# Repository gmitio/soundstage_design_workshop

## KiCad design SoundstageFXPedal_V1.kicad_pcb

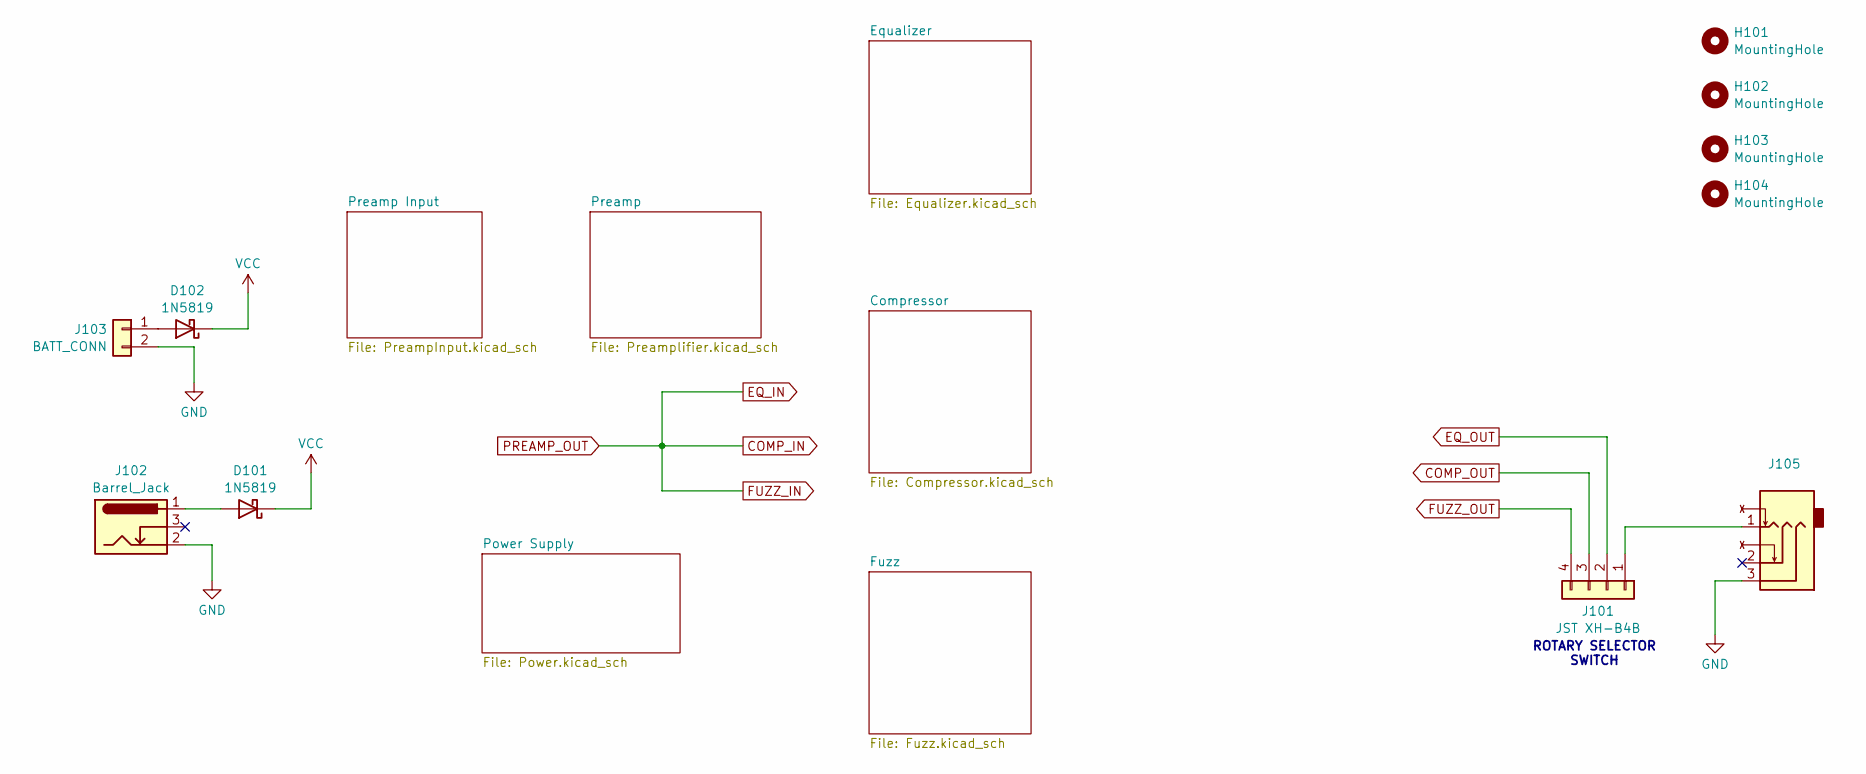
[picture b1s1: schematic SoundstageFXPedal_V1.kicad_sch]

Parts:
D101, D102: 1N5819; D_DO-41_SOD81_P10.16mm_Horizontal
H101, H102, H103, H104: MountingHole; MountingHole_4.3mm_M4_DIN965
J101: JST XH-B4B; JST_XH_B4B-XH-A_1x04_P2.50mm_Vertical
J102: Barrel_Jack; BarrelJack_Wuerth_6941xx301002
J103: BATT_CONN; PinHeader_1x02_P2.54mm_Vertical
J105: JST_XH_B3B-XH-A_1x03_P2.50mm_Vertical

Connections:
COMP_OUT: J101.3; also elsewhere on the board
EQ_OUT: J101.2; also elsewhere on the board
FUZZ_OUT: J101.4; also elsewhere on the board
GND: J102.2, J103.2, J105.3; also elsewhere on the board
unnamed: D101.2 (A), J102.1
unnamed: D102.2 (A), J103.1
unnamed: J101.1, J105.1
VCC: D101.1 (K), D102.1 (K); also elsewhere on the board

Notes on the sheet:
ROTARY SELECTOR SWITCH

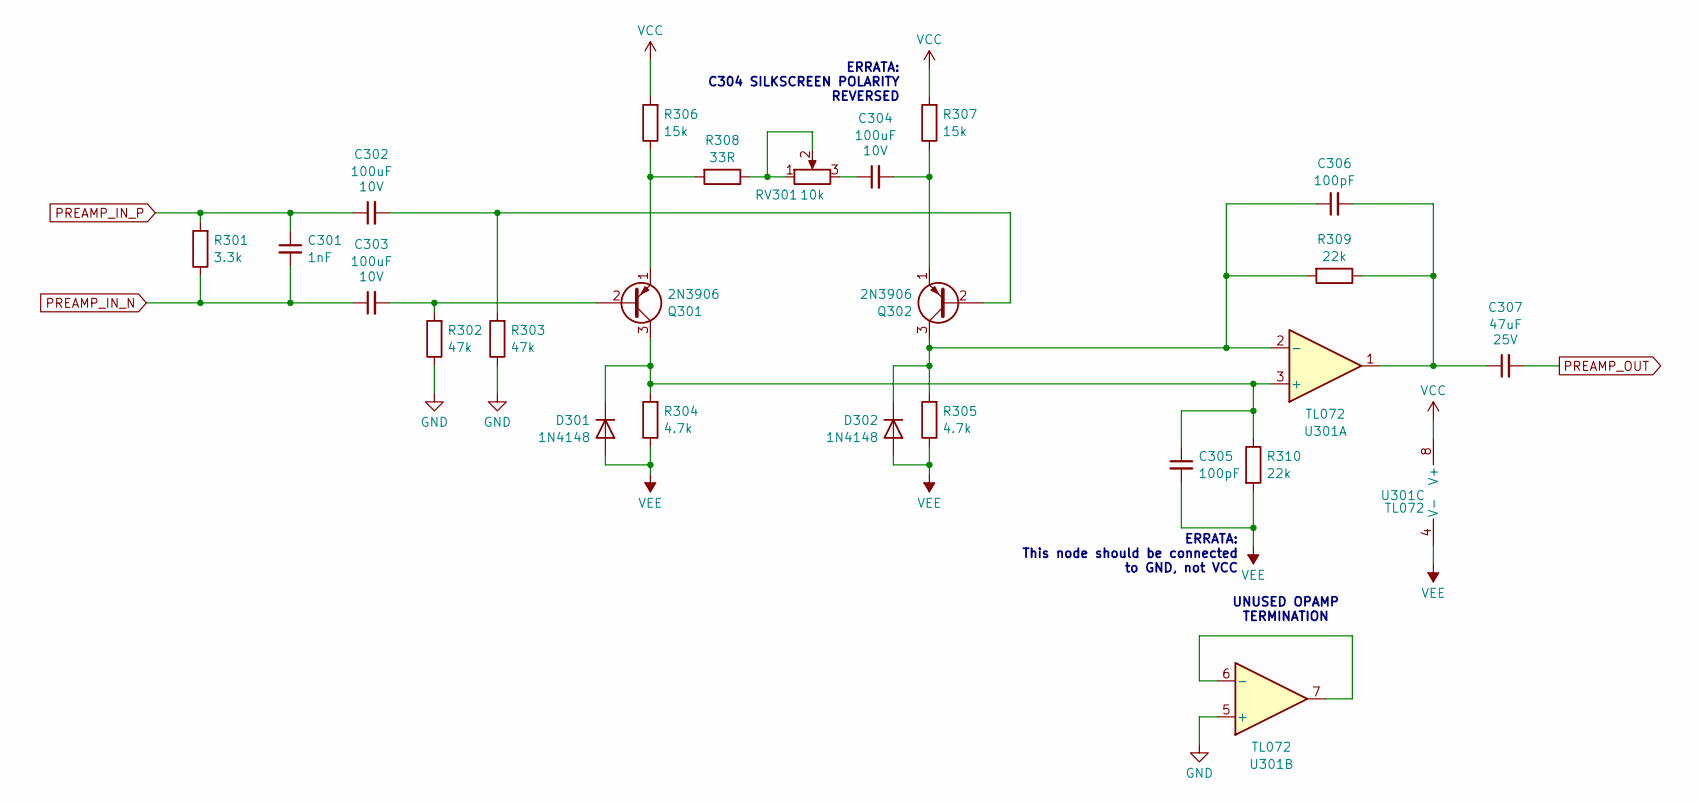
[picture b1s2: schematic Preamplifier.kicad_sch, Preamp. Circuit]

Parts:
C301: 1nF; C_Disc_D6.0mm_W4.4mm_P5.00mm
C302, C303, C304: 100uF; CP_Radial_D5.0mm_P2.00mm; Voltage 10V
C305, C306: 100pF; C_Disc_D5.0mm_W2.5mm_P2.50mm
C307: 47uF; CP_Radial_D5.0mm_P2.00mm; Voltage 25V; PartNo. MOUSER: 232-25PK47MEFC5X11
D301, D302: 1N4148; D_DO-35_SOD27_P7.62mm_Horizontal
Q301, Q302: 2N3906; TO-92_Inline_Wide
R301: 3.3k; R_Axial_DIN0207_L6.3mm_D2.5mm_P7.62mm_Horizontal
R302, R303: 47k; R_Axial_DIN0207_L6.3mm_D2.5mm_P7.62mm_Horizontal
R304, R305: 4.7k; R_Axial_DIN0207_L6.3mm_D2.5mm_P7.62mm_Horizontal
R306, R307: 15k; R_Axial_DIN0207_L6.3mm_D2.5mm_P7.62mm_Horizontal
R308: 33R; R_Axial_DIN0207_L6.3mm_D2.5mm_P7.62mm_Horizontal
R309, R310: 22k; R_Axial_DIN0207_L6.3mm_D2.5mm_P7.62mm_Horizontal
RV301: 10k; JST_XH_B3B-XH-A_1x03_P2.50mm_Vertical
U301: TL072; DIP-8_W7.62mm_LongPads

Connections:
GND: R302.1, R303.1, U301.5 (+); also elsewhere on the board
unnamed: C304.1, RV301.3
unnamed: C306.2, C307.1, R309.1, U301.1
unnamed: C305.1, D301.1 (K), Q301.3 (C), R304.2, R310.1, U301.3 (+)
unnamed: C306.1, D302.1 (K), Q302.3 (C), R305.2, R309.2, U301.2 (-)
unnamed: C303.2, Q301.2 (B), R302.2
unnamed: Q301.1 (E), R306.1, R308.2
unnamed: C302.2, Q302.2 (B), R303.2
unnamed: C304.2, Q302.1 (E), R307.1
unnamed: R308.1, RV301.1, RV301.2
unnamed: U301.6 (-), U301.7
PREAMP_IN_N: C301.2, C303.1, R301.1; also elsewhere on the board
PREAMP_IN_P: C301.1, C302.1, R301.2; also elsewhere on the board
VCC: R306.2, R307.2, U301.8 (V+); also elsewhere on the board
VEE: C305.2, D301.2 (A), D302.2 (A), R304.1, R305.1, R310.2, U301.4 (V-); also elsewhere on the board

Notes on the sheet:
ERRATA: This node should be connected to GND, not VCC
UNUSED OPAMP TERMINATION
ERRATA: C304 SILKSCREEN POLARITY REVERSED

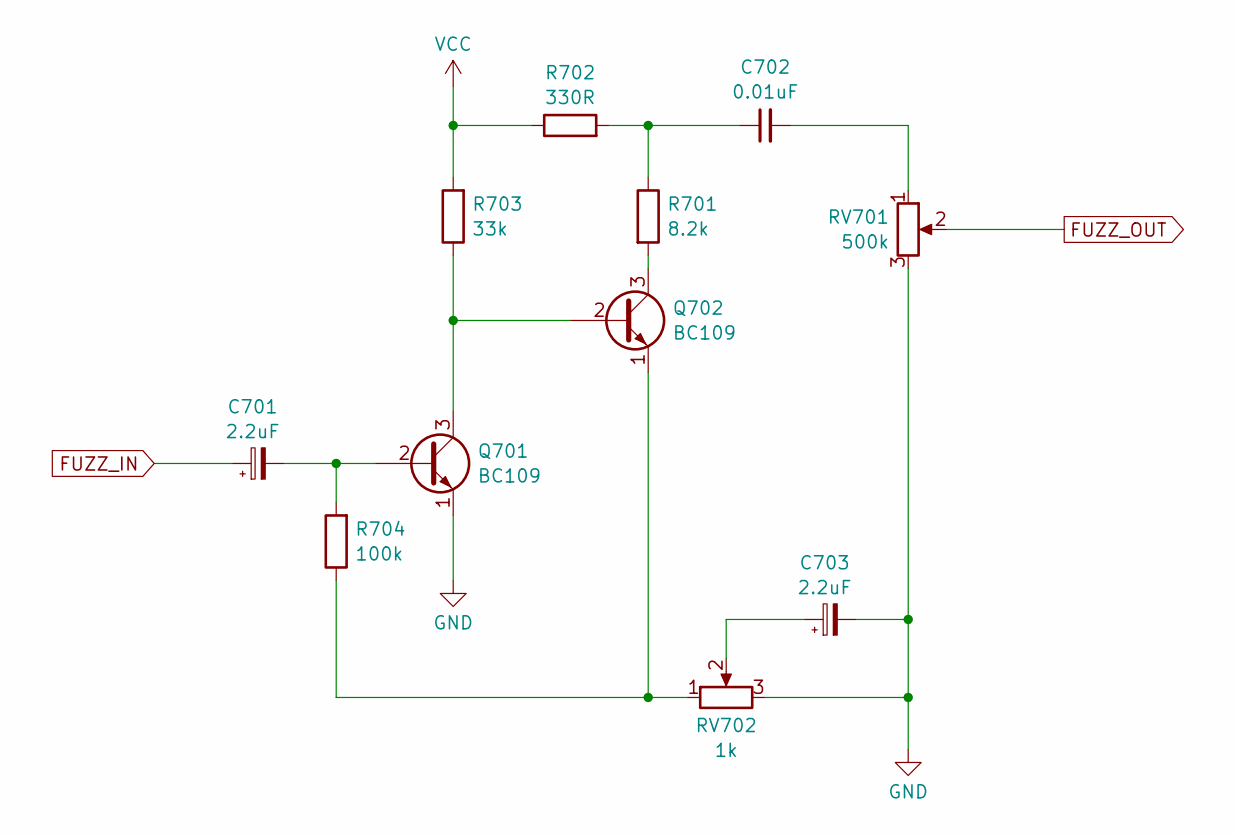
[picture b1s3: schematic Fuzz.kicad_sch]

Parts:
C701, C703: 2.2uF; CP_Radial_D5.0mm_P2.00mm
C702: 0.01uF; C_Disc_D5.0mm_W2.5mm_P2.50mm
Q701, Q702: BC109; TO-18-3
R701: 8.2k; R_Axial_DIN0207_L6.3mm_D2.5mm_P7.62mm_Horizontal
R702: 330R; R_Axial_DIN0207_L6.3mm_D2.5mm_P7.62mm_Horizontal
R703: 33k; R_Axial_DIN0207_L6.3mm_D2.5mm_P7.62mm_Horizontal
R704: 100k; R_Axial_DIN0207_L6.3mm_D2.5mm_P7.62mm_Horizontal
RV701: 500k; JST_XH_B3B-XH-A_1x03_P2.50mm_Vertical
RV702: 1k; JST_XH_B3B-XH-A_1x03_P2.50mm_Vertical

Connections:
FUZZ_OUT: RV701.2; also elsewhere on the board
GND: C703.2, Q701.1 (E), RV701.3, RV702.3; also elsewhere on the board
unnamed: C702.1, R701.1, R702.2
unnamed: C702.2, RV701.1
unnamed: C703.1, RV702.2
unnamed: C701.2, Q701.2 (B), R704.2
unnamed: Q701.3 (C), Q702.2 (B), R703.1
unnamed: Q702.3 (C), R701.2
unnamed: Q702.1 (E), R704.1, RV702.1
VCC: R702.1, R703.2; also elsewhere on the board

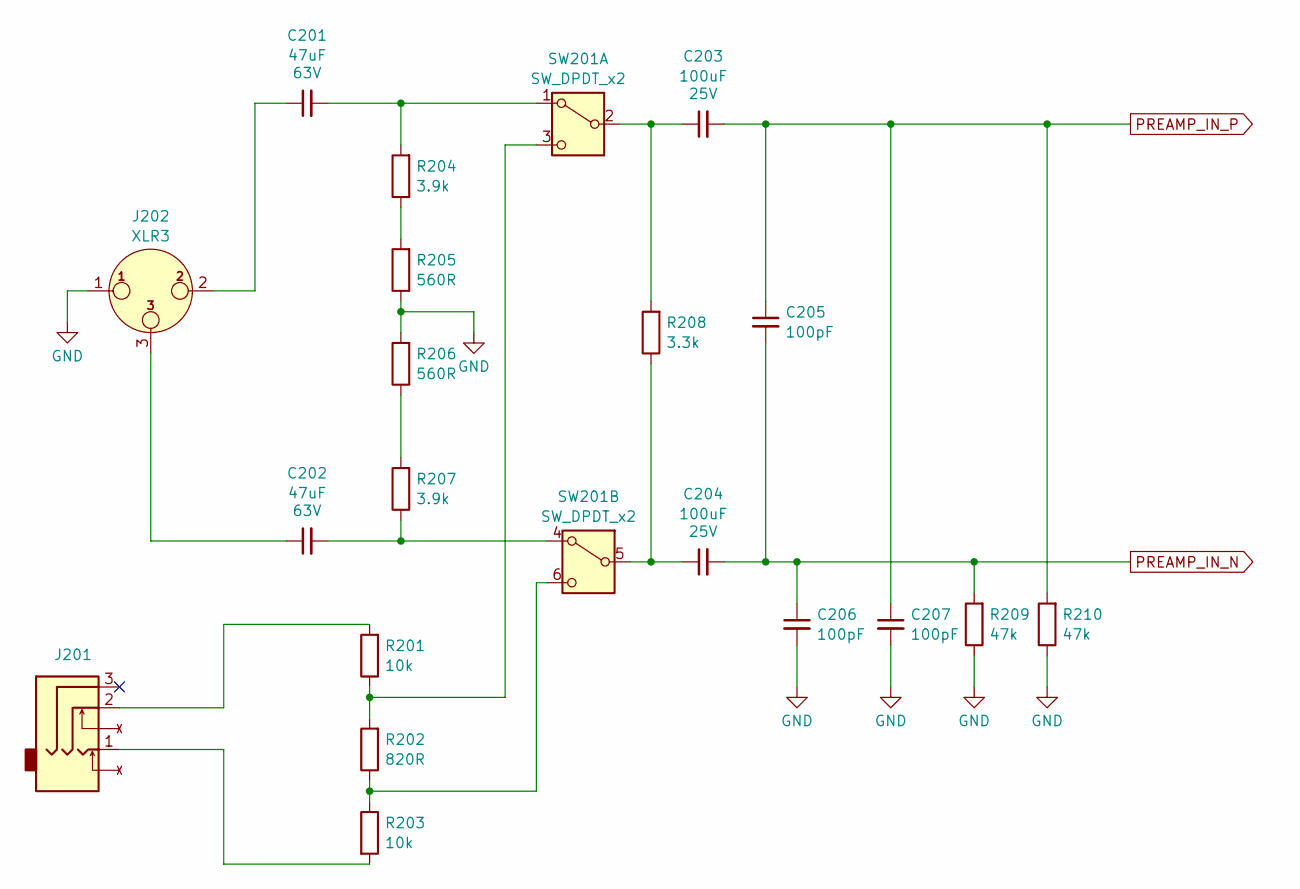
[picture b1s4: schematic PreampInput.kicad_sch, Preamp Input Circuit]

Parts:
C201, C202: 47uF; CP_Radial_D6.3mm_P2.50mm; Voltage 63V
C203, C204: 100uF; CP_Radial_D5.0mm_P2.00mm; Voltage 25V
C205, C206, C207: 100pF; C_Disc_D5.0mm_W2.5mm_P2.50mm
J201: JST_XH_B3B-XH-A_1x03_P2.50mm_Vertical
J202: XLR3; JST_XH_B3B-XH-A_1x03_P2.50mm_Vertical
R201, R203: 10k; R_Axial_DIN0207_L6.3mm_D2.5mm_P7.62mm_Horizontal
R202: 820R; R_Axial_DIN0207_L6.3mm_D2.5mm_P7.62mm_Horizontal
R204, R207: 3.9k; R_Axial_DIN0207_L6.3mm_D2.5mm_P7.62mm_Horizontal
R205, R206: 560R; R_Axial_DIN0207_L6.3mm_D2.5mm_P7.62mm_Horizontal
R208: 3.3k; R_Axial_DIN0207_L6.3mm_D2.5mm_P7.62mm_Horizontal
R209, R210: 47k; R_Axial_DIN0207_L6.3mm_D2.5mm_P7.62mm_Horizontal
SW201: SW_DPDT_x2; JST_XH_B6B-XH-A_1x06_P2.50mm_Vertical

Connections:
GND: C206.2, C207.2, J202.1, R205.1, R206.2, R209.1, R210.1; also elsewhere on the board
unnamed: C201.1, J202.2
unnamed: C202.1, J202.3
unnamed: J201.1, R203.2
unnamed: J201.2, R201.2
unnamed: R204.1, R205.2
unnamed: R206.1, R207.2
unnamed: C201.2, R204.2, SW201.1 (A)
unnamed: C203.1, R208.2, SW201.2 (B)
unnamed: R201.1, R202.2, SW201.3 (C)
unnamed: C202.2, R207.1, SW201.4 (A)
unnamed: C204.1, R208.1, SW201.5 (B)
unnamed: R202.1, R203.1, SW201.6 (C)
PREAMP_IN_N: C204.2, C205.2, C206.1, R209.2; also elsewhere on the board
PREAMP_IN_P: C203.2, C205.1, C207.1, R210.2; also elsewhere on the board

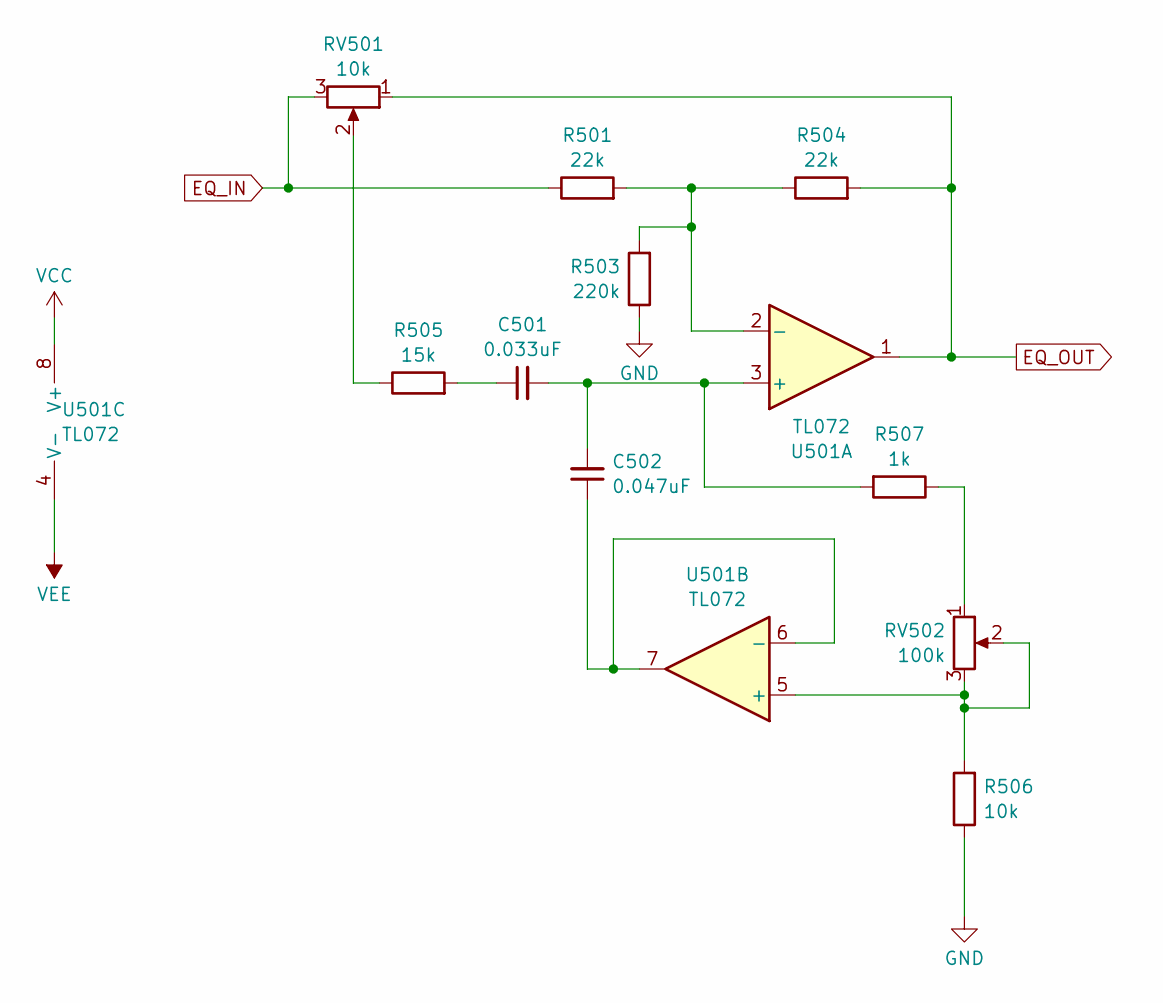
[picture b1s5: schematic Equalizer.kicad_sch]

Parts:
C501: 0.033uF; C_Disc_D5.0mm_W2.5mm_P2.50mm; PartNo. FG14C0G1H333JNT06
C502: 0.047uF; C_Disc_D5.0mm_W2.5mm_P2.50mm
R501, R504: 22k; R_Axial_DIN0207_L6.3mm_D2.5mm_P7.62mm_Horizontal
R503: 220k; R_Axial_DIN0207_L6.3mm_D2.5mm_P7.62mm_Horizontal
R505: 15k; R_Axial_DIN0207_L6.3mm_D2.5mm_P7.62mm_Horizontal
R506: 10k; R_Axial_DIN0207_L6.3mm_D2.5mm_P7.62mm_Horizontal
R507: 1k; R_Axial_DIN0207_L6.3mm_D2.5mm_P7.62mm_Horizontal
RV501: 10k; JST_XH_B3B-XH-A_1x03_P2.50mm_Vertical
RV502: 100k; JST_XH_B3B-XH-A_1x03_P2.50mm_Vertical
U501: TL072; DIP-8_W7.62mm_LongPads

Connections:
EQ_OUT: R504.2, RV501.1, U501.1; also elsewhere on the board
GND: R503.1, R506.1; also elsewhere on the board
unnamed: C501.1, R505.2
unnamed: R505.1, RV501.2
unnamed: R507.1, RV502.1
unnamed: C501.2, C502.2, R507.2, U501.3 (+)
unnamed: R501.2, R503.2, R504.1, U501.2 (-)
unnamed: R506.2, RV502.2, RV502.3, U501.5 (+)
unnamed: C502.1, U501.6 (-), U501.7
VCC: U501.8 (V+); also elsewhere on the board
VEE: U501.4 (V-); also elsewhere on the board

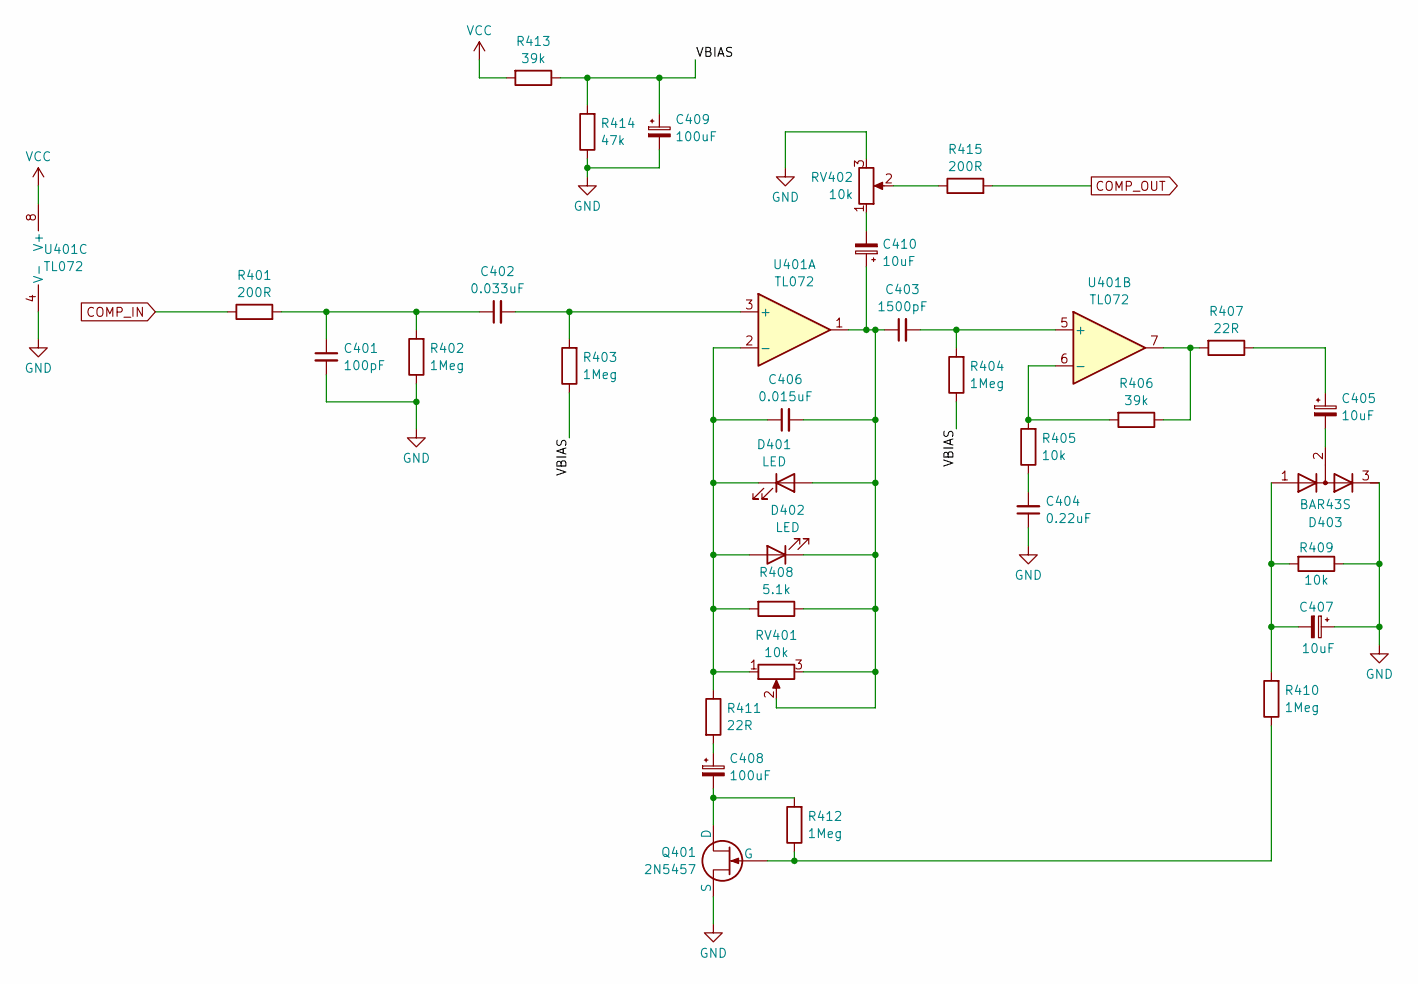
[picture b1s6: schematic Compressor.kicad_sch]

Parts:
C401: 100pF; C_Disc_D3.8mm_W2.6mm_P2.50mm; PartNo. FG18C0G1H101JNT06
C402: 0.033uF; C_Disc_D3.8mm_W2.6mm_P2.50mm; PartNo. FG14C0G1H333JNT06
C403: 1500pF; C_Disc_D6.0mm_W4.4mm_P5.00mm
C404: 0.22uF; C_Disc_D5.0mm_W2.5mm_P2.50mm
C405, C407, C410: 10uF; CP_Radial_D4.0mm_P1.50mm
C406: 0.015uF; C_Disc_D5.0mm_W2.5mm_P2.50mm
C408, C409: 100uF; CP_Radial_D5.0mm_P2.00mm
D401, D402: LED; LED_D5.0mm_FlatTop
D403: BAR43S; SOT-23; PartNo. BAR43SFILM
Q401: 2N5457; TO-92_Inline
R401, R415: 200R; R_Axial_DIN0207_L6.3mm_D2.5mm_P7.62mm_Horizontal
R402, R403, R404, R410, R412: 1Meg; R_Axial_DIN0207_L6.3mm_D2.5mm_P7.62mm_Horizontal
R405, R409: 10k; R_Axial_DIN0207_L6.3mm_D2.5mm_P7.62mm_Horizontal
R406, R413: 39k; R_Axial_DIN0207_L6.3mm_D2.5mm_P7.62mm_Horizontal
R407, R411: 22R; R_Axial_DIN0207_L6.3mm_D2.5mm_P7.62mm_Horizontal
R408: 5.1k; R_Axial_DIN0207_L6.3mm_D2.5mm_P7.62mm_Horizontal
R414: 47k; R_Axial_DIN0207_L6.3mm_D2.5mm_P7.62mm_Horizontal
RV401, RV402: 10k; JST_XH_B3B-XH-A_1x03_P2.50mm_Vertical
U401: TL072; DIP-8_W7.62mm_LongPads

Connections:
/Compressor/VBIAS: C409.1, R403.1, R404.1, R413.1, R414.2
COMP_OUT: R415.2; also elsewhere on the board
GND: C401.2, C404.1, C407.1, C409.2, D403.3 (K), Q401.3 (S), R402.1, R409.1, R414.1, RV402.3, U401.4 (V-); also elsewhere on the board
unnamed: C401.1, C402.1, R401.2, R402.2
unnamed: C404.2, R405.1
unnamed: C405.1, R407.1
unnamed: C405.2, D403.2
unnamed: C408.1, R411.2
unnamed: C410.2, RV402.1
unnamed: C403.1, C406.2, C410.1, D401.2 (A), D402.1 (K), R408.1, RV401.2, RV401.3, U401.1
unnamed: C406.1, D401.1 (K), D402.2 (A), R408.2, R411.1, RV401.1, U401.2 (-)
unnamed: C407.2, D403.1 (A), R409.2, R410.2
unnamed: C408.2, Q401.1 (D), R412.2
unnamed: Q401.2 (G), R410.1, R412.1
unnamed: R406.1, R407.2, U401.7
unnamed: R415.1, RV402.2
unnamed: C402.2, R403.2, U401.3 (+)
unnamed: C403.2, R404.2, U401.5 (+)
unnamed: R405.2, R406.2, U401.6 (-)
VCC: R413.2, U401.8 (V+); also elsewhere on the board

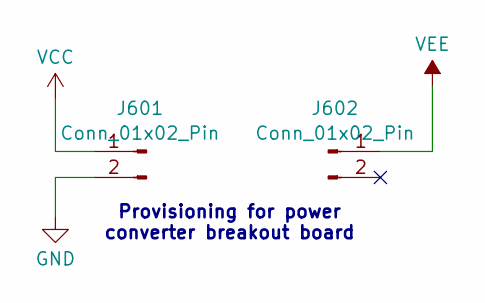
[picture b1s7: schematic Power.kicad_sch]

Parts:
J601, J602: Conn_01x02_Pin; PinHeader_1x02_P2.54mm_Vertical

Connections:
GND: J601.2; also elsewhere on the board
VCC: J601.1; also elsewhere on the board
VEE: J602.1; also elsewhere on the board

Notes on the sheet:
Provisioning for power converter breakout board

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
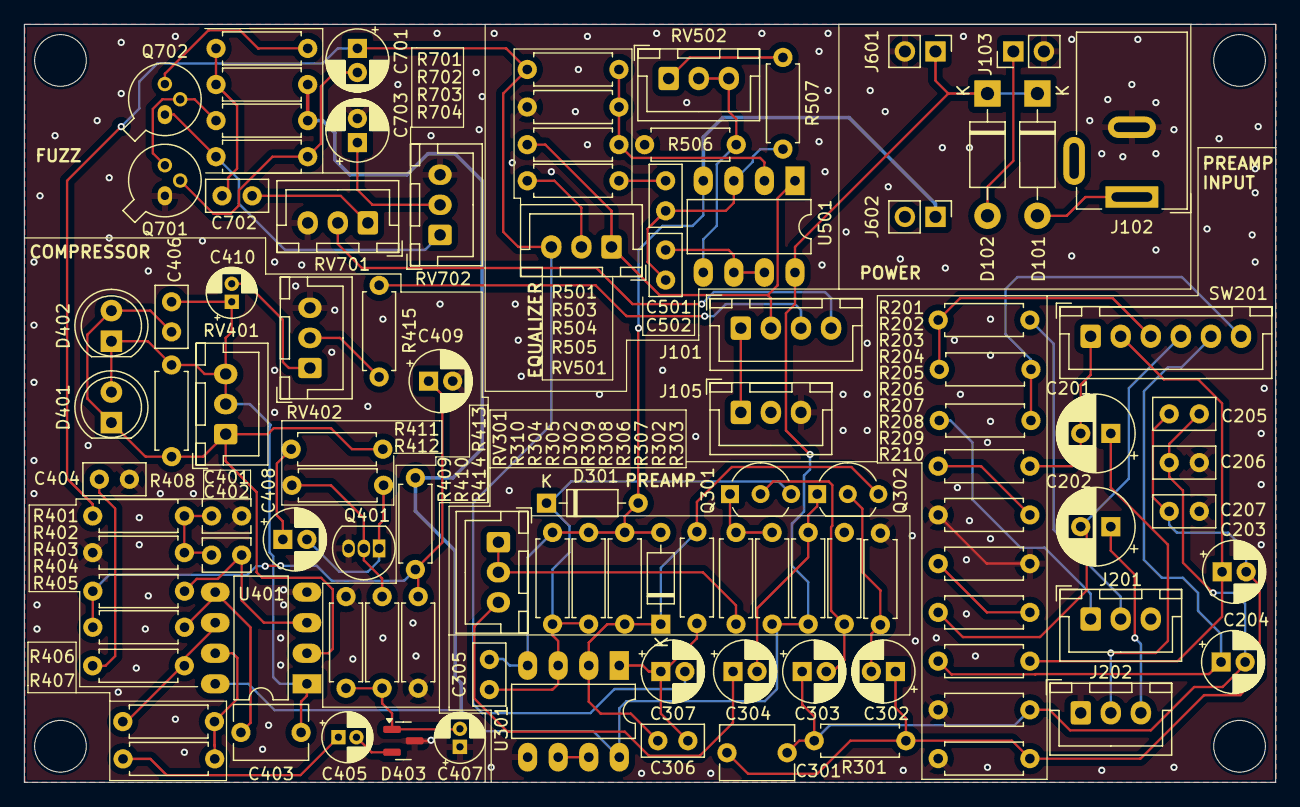
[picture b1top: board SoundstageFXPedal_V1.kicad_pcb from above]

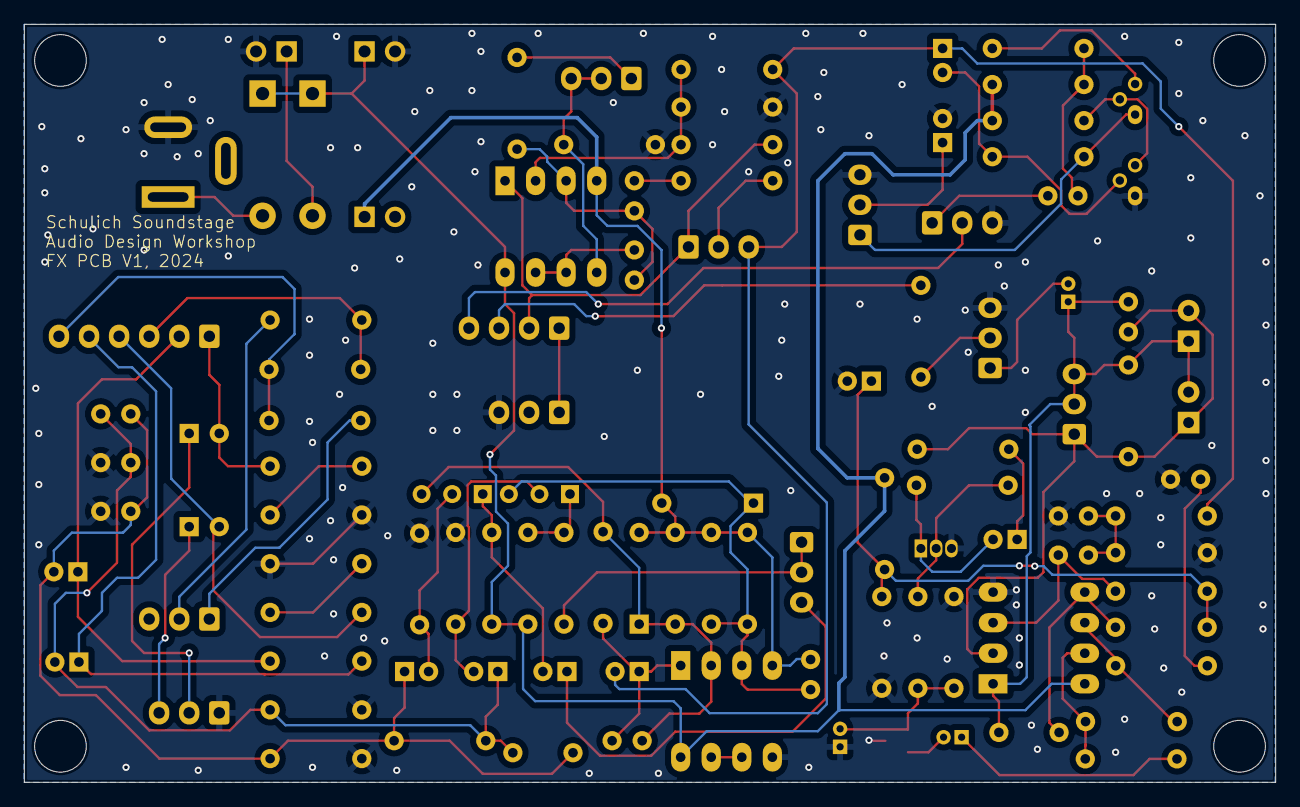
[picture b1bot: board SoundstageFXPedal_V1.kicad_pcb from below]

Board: 2 copper layers, 104.0 x 63.0 mm, 109 parts (4 on the bottom side), 65 nets.

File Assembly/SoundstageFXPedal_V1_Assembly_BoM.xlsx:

Reference | Value | Component
C201,C202 | 47uF | MOUSER: 232-63PK47MEFC6.3X11
C203,C204,C302,C303,C304,C408,C409 | 100uF | MOUSER: 232-25PX100MEFC5X11
C205,C206,C207,C305,C306,C401 | 100pF | MOUSER: 810-FG18C0G1H101JNT0
C301 | 1nF | MOUSER: 810-FG28C0G1H102JNT6
C307 | 47uF | MOUSER: 232-25PK47MEFC5X11
C402,C501 | 0.033uF | MOUSER: 810-FG14C0G1H333JNT6
C403 | 1500pF | MOUSER: 810-FG28C0G1H152JNT6
C404 | 0.22uF | MOUSER: 810-FG14X7R1H224KNT0
C405,C407,C410 | 10uF | MOUSER: 667-EEA-FC1E100
C406 | 0.015uF | MOUSER: 594-K153K15X7RF53L2
C502 | 0.047uF | MOUSER: 810-FG18X7R1H473KNT6
C701,C703 | 2.2uF | MOUSER: 667-ECA-1HM2R2
C702 | 0.01uF | MOUSER: 810-FG28C0G1H103JNT6
D101,D102 | 1N5819 | MOUSER: 637-1N5819
D301,D302 | 1N4148 | MOUSER: 512-1N4148
D401,D402 | LED | MOUSER: 606-4304H1
D403 | BAR43S | MOUSER: 511-BAR43SFILM
J101 | JST XH-B4B | MOUSER: 306-B4BXHALFSN
J102 | Barrel_Jack | MOUSER: 710-694106301002
J103 | BATT_CONN | MOUSER: 534-235
J105,J201,J202,RV301,RV401,RV402,RV501,RV502,RV701,RV702 | -- mixed values -- | MOUSER: 306-B3BXHALFSNP
J601,J602 | Conn_01x02_Pin
Q301,Q302 | 2N3906 | MOUSER: 637-2N3906
Q401 | 2N5457 | https://stompboxparts.com/semiconductors/2n5457-jfet/
Q701,Q702 | BC109 | MOUSER: 610-BC109C-TL
R201,R203,R405,R409,R506 | 10k | MOUSER: 603-MFR-25FTF52-10K
R202 | 820R | MOUSER: 603-MFR-25FBF52-820R
R204,R207 | 3.9k | MOUSER: 603-MFR-25FBF52-3K9
R205,R206 | 560R | MOUSER: 603-MFR-25FBF52-560R
R208,R301 | 3.3k | MOUSER: 603-MFR-25FRF52-3K3
R209,R210,R302,R303,R414 | 47k | MOUSER: 603-MFR-25FBF52-47K
R304,R305 | 4.7k | MOUSER: 603-MFR-25FTF52-4K7
R306,R307,R505 | 15k | MOUSER: 603-MFR-25FRF5215K
R308 | 33R | MOUSER: 603-MFR-25FBF52-33R
R309,R310,R501,R504 | 22k | MOUSER: 603-MFR-25FTF52-22K
R401,R415 | 200R | MOUSER: 603-MFR-25FBF52-200R
R402,R403,R404,R410,R412 | 1Meg | MOUSER: 603-MFR-25FTF52-1M
R406,R413 | 39k | MOUSER: 603-MFR-25FBF52-39K
R407,R411 | 22R | MOUSER: 603-MFR-25FBF52-22R
R408 | 5.1k | MOUSER: 603-MFR-25FBF52-5K1
R503 | 220k | MOUSER: 603-MFR-25FBF52-220K
R507 | 1k | MOUSER: 603-MFR-25FBF52-1K
R701 | 8.2k | MOUSER: 603-MFR-25FBF52-8K2
R702 | 330R | MOUSER: 603-MFR-25FTF52-330R
R703 | 33k | MOUSER: 603-MFR-25FBF52-33K
R704 | 100k | MOUSER: 708-RNF14FTD100K
SW201 | SW_DPDT_x2 | MOUSER: 306-B6BXHALFSN
U301,U401,U501 | TL072 | MOUSER: 595-TL072CP

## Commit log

2024-12-13 Initial commit of Soundstage FX HW Design
2024-12-17 Completed routing, cleanup, and artwork export
2025-01-26 Added schematic, assembly drawings, and assembly BoM exports
